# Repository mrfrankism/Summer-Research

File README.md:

# Summer-Research 2017

This was the start of some summer reasearch I participated at WPI.
We needed a really fast ADC to sample E-Fields around a phantom head to then back 
calculate where the applied magnetic field affected the head. When the summer ended we were working on the circuitry
and antenna to properly measure the E-field.

This code was written for Arduino, which is very C-based

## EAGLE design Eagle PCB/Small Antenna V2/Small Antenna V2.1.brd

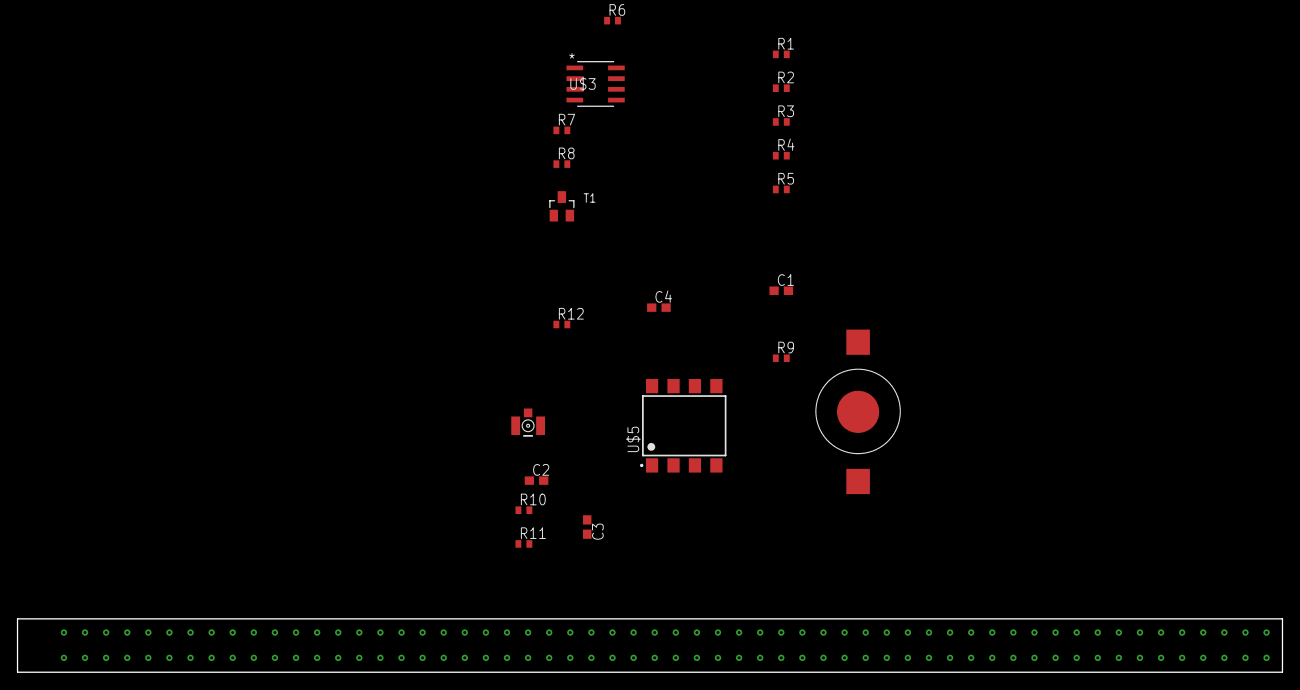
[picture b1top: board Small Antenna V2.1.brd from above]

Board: 4 copper layers, 149.9 x 6.3 mm, 21 parts (0 on the bottom side), 17 nets.

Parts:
C1, C2, C3, C4: C0603
R1, R2, R3, R4, R5, R6, R7, R8, R9, R10, R11, R12: R0402
T1: BC856; SOT23
U$3: TLV2761ID; D8
U$5: HCNR200; SOIC254P1030X390-8N
U$12: CR1025BATTERYHOLDER; BATTERYHOLDDER
X1: MC-921

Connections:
GND: U$5.5, X1.2@1, X1.2@2
unnamed: R1.2, R2.2
unnamed: R1.1, R3.2
unnamed: C1.2, R2.1, R4.2
unnamed: C1.1, R3.1, R5.2
unnamed: R4.1, R6.2, U$3.2
unnamed: R5.1, U$3.3
unnamed: R6.1, R7.2, U$3.1
unnamed: C4.2, R7.1, R8.2, U$3.6, U$5.3
unnamed: R12.2, T1.2
unnamed: C4.1, T1.1, U$3.7
unnamed: T1.3, U$5.2
unnamed: U$5.6, X1.1
VCM: C2.1, R9.2, R10.1, R11.2, U$3.5, U$5.4
VHF: C3.1, R8.1, R10.2, R12.1, U$3.8, U$12.+, U$12.+2
VHL: U$3.4, U$5.1
VLF: C2.2, C3.2, R11.1, U$12.-

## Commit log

2017-04-16 First commit to push existing files to git
2017-04-19 Saving to git
2017-04-21 Added some files to test ADC speed
2017-08-17 Adding Readme
2017-08-18 Updateing the Repo to contain all relevant files
2017-08-18 added pics
2017-08-18 Spring Cleaning
2017-08-18 Revert "commit"
    This reverts commit c194a68ffdbfdcf819d4138cff59c6af0169af34.
2017-08-18 Revert "commit"
    This reverts commit 24b7a034425d9d4f0540a5a1f6f44928aadd4c7a.
2017-08-18 Revert "Spring Cleaning"
    This reverts commit 5aee643227346105420ea12bd6b786e04cea33de.
2017-08-18 Organizing
